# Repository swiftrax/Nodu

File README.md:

# Nodu

A 60% keyboard that fits most universal cases. PCB is based on Gondolindrim's Lasgweloth

## Supported layouts

## PCB Renders
**Top**

**Bottom**

## Bill of materials (BOM)
Amount is per PCB, multiply as needed.

| LCSC part # | Description   | Value | Package  | Amount |
| ----------- | ------------- | ----- | -------- | ------:|
| C14663      | Capacitor     | 0.1uF | 0603     | 3      |
| C19702      | Capacitor     | 10uF  | 0603     | 1      |
| C15849      | Capacitor     | 1uF   | 0603     | 1      |
| C68978      | Diode         |       | SOT-23-3 | 32     |
| C70076      | Fuse          |       | 1206     | 1      |
| C165948     | Connector     |       | SMD/THT  | 1      |
| C25804      | Resistor      | 10K   | 0603     | 2      |
| C23186      | Resistor      | 5.1K  | 0603     | 2      |
| C23345      | Resistor      | 22    | 0603     | 2      |
| C44854      | MCU           | 32U4  | QFP-44   | 1      |
| C12333      | ESD chip      |       | SOT-143B | 1      |
| C341521     | Resonator     | 16MHz | SMD      | 1      |

## License

This repository is under the [CC0 1.0 Universal License](https://github.com/swiftrax/Nodu/blob/main/LICENSE). If you plan to sell these pcbs, make sure to read it.

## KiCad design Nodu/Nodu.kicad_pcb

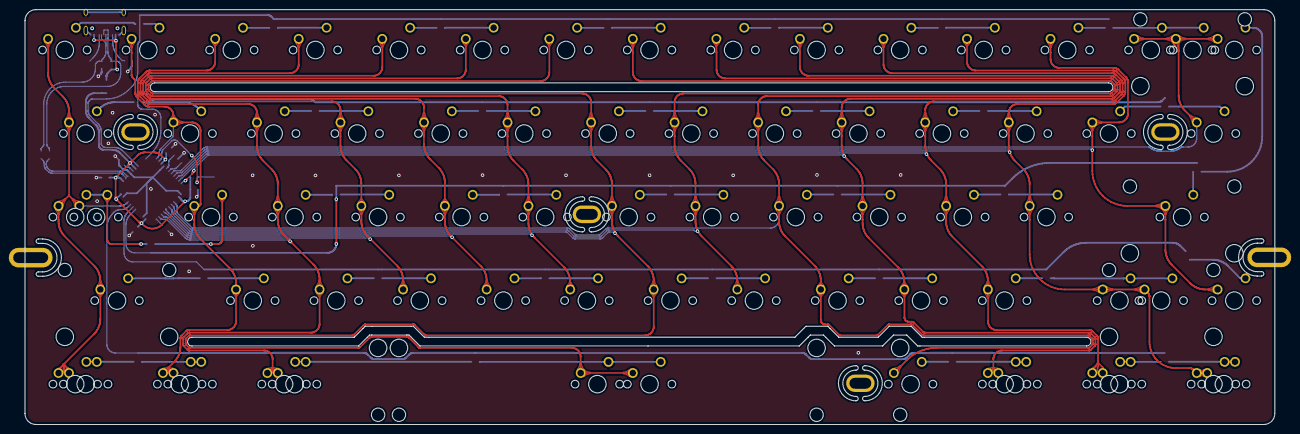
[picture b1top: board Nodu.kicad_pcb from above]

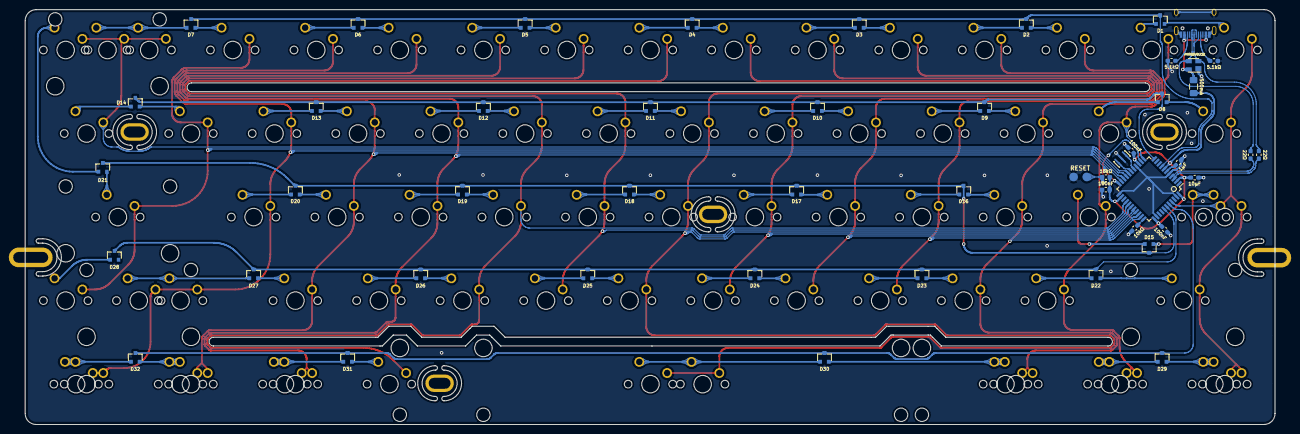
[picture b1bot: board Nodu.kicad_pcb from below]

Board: 2 copper layers, 285.0 x 94.6 mm, 128 parts (49 on the bottom side), 96 nets.

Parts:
C1: 10µF; C_0603_Annotated
C2, C3, C4: 100nF; C_0603_Annotated
C5: 1µF; C_0603_Annotated
D1, D2, D3, D4, D5, D6, D7, D8, D9, D10, D11, D12, D13, D14, D15, D16, D17, D18, D19, D20, D21, D22, D23, D24, D25, D26, D27, D28, D29, D30, D31, D32: BAV70; SOT-23_Annotated
ESD1: PRTR5V0U2X; SOT-143
F1: 500mA; Fuse_1206_Annotated
H1: M2 Slot; Flex_M2_Left
H2: M2 Slot; Flex_M2_Right
H3, H4, H5, H6: M2 Screw; Flex_M2_Hole
K_0: KC_ESC; MXOnly-1U-NoLED
K_1: KC_1; MXOnly-1U-NoLED
K_2: KC_2; MXOnly-1U-NoLED
K_3: KC_3; MXOnly-1U-NoLED
K_4: KC_4; MXOnly-1U-NoLED
K_5: KC_5; MXOnly-1U-NoLED
K_6: KC_6; MXOnly-1U-NoLED
K_7: KC_7; MXOnly-1U-NoLED
K_8: KC_8; MXOnly-1U-NoLED
K_9: KC_9; MXOnly-1U-NoLED
K_10: KC_0; MXOnly-1U-NoLED
K_11: KC_MINS; MXOnly-1U-NoLED
K_12: KC_EQL; MXOnly-1U-NoLED
K_13: KC_BSPC; MXOnly-2U-NoLED
K_013A1: KC_BSPC; MXOnly-1U-NoLED
K_100: KC_TAB; MXOnly-1.5U-NoLED
K_101: KC_Q; MXOnly-1U-NoLED
K_102: KC_W; MXOnly-1U-NoLED
K_103: KC_E; MXOnly-1U-NoLED
K_104: KC_R; MXOnly-1U-NoLED
K_105: KC_T; MXOnly-1U-NoLED
K_106: KC_Y; MXOnly-1U-NoLED
K_107: KC_U; MXOnly-1U-NoLED
K_108: KC_I; MXOnly-1U-NoLED
K_109: KC_O; MXOnly-1U-NoLED
K_110: KC_P; MXOnly-1U-NoLED
K_111: KC_LBRC; MXOnly-1U-NoLED
K_112: KC_RBRC; MXOnly-1U-NoLED
K_113: KC_BSLS; MXOnly-1.5U-NoLED
K_200: KC_CAPS; MXOnly-1.75U-NoLED
K_200A1: KC_CAPS; MXOnly-1.25U-NoLED
K_201: KC_A; MXOnly-1U-NoLED
K_202: KC_S; MXOnly-1U-NoLED
K_203: KC_D; MXOnly-1U-NoLED
K_204: KC_F; MXOnly-1U-NoLED
K_205: KC_G; MXOnly-1U-NoLED
K_206: KC_H; MXOnly-1U-NoLED
K_207: KC_J; MXOnly-1U-NoLED
K_208: KC_K; MXOnly-1U-NoLED
K_209: KC_L; MXOnly-1U-NoLED
K_210: KC_SCLN; MXOnly-1U-NoLED
K_211: KC_QUOT; MXOnly-1U-NoLED
K_212: KC_ENT; MXOnly-2.25U-NoLED
K_213: KC_DEL; MXOnly-1U-NoLED
K_300: KC_LSFT; MXOnly-2.25U-NoLED
K_301: KC_Z; MXOnly-1U-NoLED
K_302: KC_X; MXOnly-1U-NoLED
K_303: KC_C; MXOnly-1U-NoLED
K_304: KC_V; MXOnly-1U-NoLED
K_305: KC_B; MXOnly-1U-NoLED
K_306: KC_N; MXOnly-1U-NoLED
K_307: KC_M; MXOnly-1U-NoLED
K_308: KC_COMM; MXOnly-1U-NoLED
K_309: KC_DOT; MXOnly-1U-NoLED
K_310: KC_SLSH; MXOnly-1U-NoLED
K_311: KC_RSFT; MXOnly-2.75U-NoLED
K_311A1: KC_RSFT; MXOnly-1.75U-NoLED
K_312, K_410A1: KC_MO(1); MXOnly-1U-NoLED
K_400: KC_LCTL; MXOnly-1.25U-NoLED
K_400A1: KC_LCTL; MXOnly-1.5U-NoLED
K_401: KC_LGUI; MXOnly-1.25U-NoLED
K_401A1: KC_LGUI; MXOnly-1U-NoLED
K_402: KC_LALT; MXOnly-1.25U-NoLED
K_402A1: KC_LALT; MXOnly-1.5U-NoLED
K_406: KC_SPC; MXOnly-6.25U-ReversedStabilizers-NoLED
K_406A1: KC_SPC; MXOnly-7U-ReversedStabilizers-NoLED
K_408: KC_RALT; MXOnly-1.25U-NoLED
K_409: KC_RGUI; MXOnly-1.25U-NoLED
K_409A1: KC_RALT; MXOnly-1.5U-NoLED
K_410: KC_MO(1); MXOnly-1.25U-NoLED
K_411: KC_RCTL; MXOnly-1.25U-NoLED
K_411A1: KC_RCTL; MXOnly-1.5U-NoLED
R1, R2: 10kΩ; R_0603_Annotated
R3, R4: 22Ω; R_0603_Annotated
R5, R6: 5.1kΩ; R_0603_Annotated
SW1: RESET; RESET_PADS
U1: ATmega32U4-AU; ATMEGA32U4_Annotated
USB1: HRO-TYPE-C-31-M-12
Y1: 16MHz; Resonator_3Pin_Annotated

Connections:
+5V: C1.1, C2.1, C3.1, C4.1, F1.1, R1.1, U1.2, U1.7, U1.14, U1.24, U1.34, U1.44
DA+: R3.1, U1.4
DA-: R4.1, U1.3
DB+: ESD1.3, R3.2, USB1.6, USB1.8
DB-: ESD1.2, R4.2, USB1.5, USB1.7
GND: C1.2, C2.2, C3.2, C4.2, C5.2, ESD1.1, R2.1, R5.1, R6.1, SW1.1, U1.5, U1.15, U1.23, U1.35, U1.43, USB1.1, USB1.12, USB1.13, Y1.2
unnamed: C5.1, U1.6
unnamed: D1.1, K_1.2
unnamed: D1.2, K_0.2
unnamed: D2.1, K_3.2
unnamed: D2.2, K_2.2
unnamed: D3.1, K_5.2
unnamed: D3.2, K_4.2
unnamed: D4.1, K_7.2
unnamed: D4.2, K_6.2
unnamed: D5.1, K_9.2
unnamed: D5.2, K_8.2
unnamed: D6.1, K_11.2
unnamed: D6.2, K_10.2
unnamed: D7.1, K_13.2, K_013A1.2
unnamed: D7.2, K_12.2
unnamed: D8.1, K_101.2
unnamed: D8.2, K_100.2
unnamed: D9.1, K_103.2
unnamed: D9.2, K_102.2
unnamed: D10.1, K_105.2
unnamed: D10.2, K_104.2
unnamed: D11.1, K_107.2
unnamed: D11.2, K_106.2
unnamed: D12.1, K_109.2
unnamed: D12.2, K_108.2
unnamed: D13.1, K_111.2
unnamed: D13.2, K_110.2
unnamed: D14.1, K_113.2
unnamed: D14.2, K_112.2
unnamed: D15.1, K_200.2, K_200A1.2
unnamed: D15.2, K_201.2
unnamed: D16.1, K_203.2
unnamed: D16.2, K_202.2
unnamed: D17.1, K_205.2
unnamed: D17.2, K_204.2
unnamed: D18.1, K_207.2
unnamed: D18.2, K_206.2
unnamed: D19.1, K_209.2
unnamed: D19.2, K_208.2
unnamed: D20.1, K_211.2
unnamed: D20.2, K_210.2
unnamed: D21.1, K_213.2
unnamed: D21.2, K_212.2
unnamed: D22.1, K_301.2
unnamed: D22.2, K_300.2
unnamed: D23.1, K_303.2
unnamed: D23.2, K_302.2
unnamed: D24.1, K_305.2
unnamed: D24.2, K_304.2
unnamed: D25.1, K_307.2
unnamed: D25.2, K_306.2
unnamed: D26.1, K_309.2
unnamed: D26.2, K_308.2
unnamed: D27.1, K_311.2, K_311A1.2
unnamed: D27.2, K_310.2
unnamed: D28.1, K_312.2
unnamed: D29.1, K_401.2, K_401A1.2
unnamed: D29.2, K_400.2, K_400A1.2
unnamed: D30.1, K_406.2, K_406A1.2
unnamed: D30.2, K_402.2, K_402A1.2
unnamed: D31.1, K_409.2, K_409A1.2
unnamed: D31.2, K_408.2
unnamed: D32.1, K_411.2, K_411A1.2
unnamed: D32.2, K_410.2, K_410A1.2
unnamed: R1.2, SW1.2, U1.13
unnamed: R2.2, U1.33
unnamed: R5.2, USB1.4
unnamed: R6.2, USB1.10
unnamed: U1.16, Y1.3
unnamed: U1.17, Y1.1
VCC: ESD1.4, F1.2, USB1.2, USB1.11
col0: K_0.1, K_100.1, K_200.1, K_200A1.1, K_300.1, K_400.1, K_400A1.1, U1.41
col1: K_1.1, K_101.1, K_201.1, K_301.1, K_401.1, K_401A1.1, U1.12
col2: K_2.1, K_102.1, K_202.1, K_302.1, K_402.1, K_402A1.1, U1.32
col3: K_3.1, K_103.1, K_203.1, K_303.1, U1.31
col4: K_4.1, K_104.1, K_204.1, K_304.1, U1.30
col5: K_5.1, K_105.1, K_205.1, K_305.1, U1.29
col6: K_6.1, K_106.1, K_206.1, K_306.1, K_406.1, K_406A1.1, U1.28
col7: K_7.1, K_107.1, K_207.1, K_307.1, U1.27
col8: K_8.1, K_108.1, K_208.1, K_308.1, K_408.1, U1.26
col9: K_9.1, K_109.1, K_209.1, K_309.1, K_409.1, K_409A1.1, U1.22
col10: K_10.1, K_110.1, K_210.1, K_310.1, K_410.1, K_410A1.1, U1.21
col11: K_11.1, K_111.1, K_211.1, K_311.1, K_311A1.1, K_411.1, K_411A1.1, U1.20
col12: K_12.1, K_112.1, K_212.1, K_312.1, U1.19
col13: K_13.1, K_013A1.1, K_113.1, K_213.1, U1.18
row0: D1.3, D2.3, D3.3, D4.3, D5.3, D6.3, D7.3, U1.8
row1: D8.3, D9.3, D10.3, D11.3, D12.3, D13.3, D14.3, U1.11
row2: D15.3, D16.3, D17.3, D18.3, D19.3, D20.3, D21.3, U1.38
row3: D22.3, D23.3, D24.3, D25.3, D26.3, D27.3, D28.3, U1.39
row4: D29.3, D30.3, D31.3, D32.3, U1.40

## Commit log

2020-12-12 Add flex cutouts
2020-12-12 Layout of switches
2020-12-12 Layout Diodes + add flex cuts
2020-12-12 Fix Edgecuts
2020-12-12 Add MCU + USB circuits
2020-12-12 Add Footprints + 3D models
2020-12-13 MCU placement
2020-12-13 Route Cols
2020-12-13 Change reset pads
2020-12-13 Route Matrix
2020-12-13 Add teardrops
2020-12-14 Make Step file
2020-12-14 Fix routing
2020-12-14 Add Plate + Gerbers
2020-12-14 Add Art + generate new gerbers
2020-12-15 Add stuff for rendering
2020-12-24 Rename
2020-12-24 Add gerbers
2020-12-24 Add finished files
2020-12-24 Add renders
2020-12-25 Create LICENSE
2020-12-25 Update LICENSE
2021-01-11 rendering stuff
